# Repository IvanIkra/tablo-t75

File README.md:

<h1 align="center">Tablo T75</h1>

<p align="center">
  <b>A 7.5″ e-ink panel that shows your day at a glance — with eight real buttons for your home.</b>
</p>

<p align="center">

</p>

<p align="center">
  <a href="#whats-on-the-screen">Screen</a> ·
  <a href="#features">Features</a> ·
  <a href="#how-it-works">How it works</a> ·
  <a href="#hardware">Hardware</a> ·
  <a href="#quick-start">Quick start</a> ·
  <a href="#documentation">Docs</a>
</p>

---

Tablo is a desk or wall panel built around a 7.5″ black-and-white e-ink screen
(800×480). It shows the time, the weather for the next hours, upcoming deadlines,
news, fresh grades, the class schedule and the state of the home. Eight mechanical
keys under the screen control Home Assistant, and the tile above each key shows
whether the thing it controls is on. It runs from USB-C around the clock and reads
like a sheet of paper: no glow, no flicker.

The whole project is open: the Python service, the ESP32 firmware, the Home Assistant
integration and the 3D-printable enclosure.

## What's on the screen

<p align="center"><sub>A real frame from the service, captured in the browser emulator with demo data. Dark theme is the default.</sub></p>

| Zone | What it shows |
|---|---|
| **Clock and date** | Drawn by the board itself and updated every minute, together with the status icons (Wi-Fi, service, Home Assistant). |
| **Weather** | Now and "feels like", plus an 8-hour forecast from [Open-Meteo](https://open-meteo.com/). |
| **Deadlines** | The nearest ones first; anything due today or tomorrow is highlighted. |
| **News** | A short digest, wrapped and trimmed to fit the column. |
| **Classes** | Today's or tomorrow's classes from an iCal feed, with moved and optional ones marked. |
| **Grades** | The latest grades, with a counter of new ones. |
| **Home** | Any Home Assistant values you like: temperature, how many lights are on, the 3D printer's progress. |
| **Button tiles** | One icon per key; a filled tile means the device is on. |

<details>
<summary><b>Light theme</b></summary>
<br>

</details>

## Features

- **Smart server, dumb device.** A Python service lays out every frame with Pillow
  and streams it to the board; the ESP32 only shows it. All the logic can change
  without reflashing.
- **Partial refresh by diff.** The board compares each new frame with the one on
  the panel and redraws only what changed, with a full refresh now and then to
  clear ghosting.
- **Instant buttons.** A key press inverts its tile on the board right away, before
  the service even answers. Short and long presses can do different things.
- **Configured from Home Assistant.** Button actions, icons, Wi-Fi, data sources,
  the Home block and the screen settings are all forms in the integration.
- **Full-screen messages.** Show a message from any automation, or a sticky one that
  waits in a queue until someone presses a key.
- **Wi-Fi QR for guests.** One key shows QR codes for your networks.
- **Over-the-air updates** through the service, with a "what's new" screen after
  each new firmware version.
- **A browser emulator** of the whole board, keys included, so the screen can be
  developed without the hardware.
- **A flat printed enclosure** that hangs on the wall or stands on the desk on a
  hidden 15° leg.

<table>
  <tr>
    <td align="center" width="50%"><br><sub>A sticky message from an automation</sub></td>
    <td align="center" width="50%"><br><sub>Wi-Fi QR codes for guests</sub></td>
  </tr>
</table>

## How it works

```mermaid
flowchart LR
    subgraph sources[Data sources]
        W[Open-Meteo<br/>weather]
        I[Study data API<br/>deadlines · news · grades]
        C[iCal feed<br/>classes]
    end
    HA[Home Assistant]
    S[Tablo service<br/>Python · asyncio · Pillow]
    B[ESP32 board]
    P[(E-ink panel<br/>800×480)]

    W --> S
    I --> S
    C --> S
    HA <-->|states, config,<br/>button events| S
    S -->|1-bit frame<br/>over WebSocket| B
    B -->|key presses| S
    B --> P
```

- **The frame** is 800×480 at 1 bit per pixel: 48 000 bytes behind a small `TBLF`
  header, `1` = black. The service sends a new one only when something changes.
- **The board** keeps its own clock, date and status line, so it stays useful when
  the service is down, and it inverts the whole picture for the dark theme.
- **Buttons 1–7** do whatever Home Assistant tells them to (toggle a light, run a
  script, show the Wi-Fi QR). **Button 8** is fixed: a full refresh, or the
  diagnostics screen on a long press.
- **Secrets** live only in `.env` and in Home Assistant, never in the repository.

## Hardware

<table>
  <tr>
    <td align="center" width="33%"><br><sub>The real thing, running</sub></td>
    <td align="center" width="33%"><br><sub>On the wall</sub></td>
    <td align="center" width="33%"><br><sub>What's inside</sub></td>
  </tr>
  <tr>
    <td align="center" colspan="3"><br><sub>On the desk, on its hidden leg</sub></td>
  </tr>
</table>

| Part | What |
|---|---|
| Screen | Good Display **GDEY075T7**, 7.5″, 800×480, black and white |
| Board | Good Display **ESP32-L(C02)** with the **DESPI-C02** adapter |
| Keys | 8 × **Kailh Choc v1** Brown, low-profile |
| Power | USB-C, 5 V, any 1 A supply |
| Enclosure | 185 × 146 × 17 mm, printed in PLA or PETG without supports |

The enclosure is a parametric [OpenSCAD model](cad/tablo.scad). Ready STLs, the
list of fasteners and the print and assembly guide are in [`cad/`](cad/README.md);
the full bill of materials is in [`docs/hardware.md`](docs/hardware.md#bill-of-materials).

## Quick start

### Try it in the browser

No hardware needed: the service ships with a board emulator and a fake home.

```bash
cd service
uv sync
uv run python -m tablo --config config.yaml
```

Open <http://localhost:8765/emu>. Keys 1–8 on the keyboard press the buttons;
hold one for a long press. Checkboxes under the screen switch each block between
demo and real data. More in [`service/README.md`](service/README.md).

### Run it for real

1. **Service.** Copy `service/.env.example` to `service/.env`, fill in the tokens
   and run it with Docker: `docker compose up -d --build` in `service/`.
2. **Firmware.** Copy `firmware/include/secrets.example.h` to `secrets.h`, set
   Wi-Fi, the service address and the device token, then flash over USB:
   `pio run -e esp32 -t upload`. Later updates go over the air through the service.
3. **Home Assistant.** Copy `ha-integration/custom_components/tablo` into your HA
   config, restart HA and add the **Tablo T75** integration. See
   [`ha-integration/README.md`](ha-integration/README.md).

## Repository layout

| Path | What |
|---|---|
| [`service/`](service/) | The Python service (asyncio, aiohttp, Pillow, SQLite): data sources, layout, the device protocol, the browser emulator and the tests. |
| [`firmware/`](firmware/) | ESP32 firmware (PlatformIO + Arduino): frame buffers and diffing, the on-board clock and status line, keys, diagnostics and OTA. |
| [`ha-integration/`](ha-integration/) | The Home Assistant custom component: config forms, device triggers, `tablo.*` actions, sensors and events. |
| [`cad/`](cad/) | The enclosure in OpenSCAD, with STLs and preview renders. |
| [`docs/`](docs/) | The design documents: hardware, and the software contract split by area. |
| [`presentation/`](presentation/) | Product renders and the project presentation. |

## Documentation

| Document | About |
|---|---|
| [Product and hardware](docs/hardware.md) | What Tablo does, the screen grid, the keys, the parts and the enclosure. |
| [Architecture](docs/software/01-architecture.md) | The system and who draws which zone of the screen. |
| [Protocol](docs/software/02-protocol.md) | Board ↔ service messages, buttons and full-screen overlays. |
| [Service](docs/software/03-service.md) | Stack, layout, HTTP API and config. |
| [Data sources](docs/software/04-sources.md) | Deadlines, news, grades, classes, weather and the home. |
| [Home Assistant](docs/software/05-ha-integration.md) | The integration: forms, actions, triggers, entities. |
| [Emulator and firmware](docs/software/06-emulator-firmware.md) | The browser emulator and the ESP32 firmware. |
| [Failures and deployment](docs/software/07-failures-deploy.md) | What happens when things break, deployment and secrets. |
| [Plan](docs/software/08-plan.md) | The work plan and open questions. |

## Status

The hardware is built and running: the panel lives in its printed enclosure and
shows live frames, the clock, the status line and all eight keys, with diagnostics,
OTA updates and the post-update greeting. The firmware is at **fw-0.7**; what's
left is tuning when the panel switches from partial to full refresh.

## License

[MIT](LICENSE). Bundled third-party assets keep their own licenses:
the [Inter](service/assets/fonts/Inter-LICENSE.txt) font (SIL OFL 1.1) and the
[Material Design Icons](service/assets/mdi/LICENSE) font (Pictogrammers Free License).

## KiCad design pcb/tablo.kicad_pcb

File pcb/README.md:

# Tablo main board

KiCad 10 project for Tablo's own board: ESP32-S3 module, LiPo charger and fuel gauge, 3.3 V buck-boost, the e-paper booster circuit and the 8 key switches on one long board. The design notes, parts and pin map are in [`../docs/hardware.md`](../docs/hardware.md#custom-board-in-design); the matching enclosure is `board = "custom"` in [`../cad/`](../cad/README.md#for-the-custom-board).

Status: the schematic passes ERC; the layout is fully routed and passes DRC with the schematic parity check (left: silkscreen warnings and four thermal reliefs with one spoke). Not ordered, nothing is tried on hardware yet; see "Before ordering" below.

DRC also shows silkscreen warnings (labels over pads and the board edge) and four thermal reliefs with one spoke; none of them affects the copper.

| File | What |
|---|---|
| `tablo.kicad_sch` | The schematic (one A3 sheet, nets joined by labels) |
| `tablo.kicad_pcb` | The board: 173.5 × 41.6 mm, 4 layers (signals on F.Cu and B.Cu, solid planes: GND on In1, 3.3 V on In2) |
| `tablo.kicad_sym` | Parts missing from the KiCad libraries: TPS63802, MAX17048 |
| `tablo.pretty/` | Footprints missing from the KiCad libraries: `Kailh_Choc_V1`, `Texas_DLA0010A_VSON-HR-10_2x3mm` (from the TPS63802 datasheet's example layout) |
| `bom-parts.csv` | Manufacturer part numbers by value and footprint, and which parts are not fitted (DNP) |
| `order-notes.md` | Notes for the board house and the assembler; goes into the order package as its README |
| `tools/` | The scripts that produced the drafts, the Freerouting round trip, and the order package |

## How the drafts were made

The scripts only bootstrap the design. Once a file is edited by hand in KiCad, edit it there and do not re-run the script that wrote it, or the edits are lost.

```bash
# schematic and the custom symbols
python3 pcb/tools/gen_schematic.py
# netlist -> board: outline from the enclosure, placement, planes
kicad-cli sch export netlist --format kicadsexpr -o tablo.net pcb/tablo.kicad_sch
KPY=/Applications/KiCad/KiCad.app/Contents/Frameworks/Python.framework/Versions/Current/bin/python3
$KPY pcb/tools/gen_board.py build tablo.net
# routing: a small grid router (A* on a 0.05 mm grid; F.Cu, B.Cu and In2 when needed; vias to the planes)
$KPY pcb/tools/gen_board.py export geom.json
uv run --no-project --with numpy --with scipy python pcb/tools/route.py geom.json routes.json short
$KPY pcb/tools/gen_board.py apply routes.json
```

The router routes the signals of the fine-pitch parts first, then the power nets, then the rest; what fails gets a second pass with cheaper vias and a rip-up of the nets in its way (undone if they cannot be routed again), and GND and 3.3 V pads get short stubs to vias into the planes. `route.py finish geom.json routes.json out.json NET:REF.NUM ...` keeps a result and only tries the listed connections again. Each run takes about 10 minutes; the order (`short` or `long`) changes the result, so it is worth running both.

That draft left three connections open (around the FPC connector, where PREVGH and PREVGL boxed in VSH1 and VSL, and a piece of the 3.3 V plane cut off by tracks on In2). The committed board is that draft with part of it rerouted by [Freerouting](https://github.com/freerouting/freerouting) 2.5.0: the nets around the FPC and every net that had tracks on In2 were taken out and routed again on F.Cu and B.Cu only, so both inner layers are now solid planes. Freerouting necks power tracks down near pads and keeps only the track clearance from the FPC slot, so the script grows the slot's keepout and widens the power segments back afterwards:

```bash
$KPY pcb/tools/freeroute.py export pcb/tablo.kicad_pcb board.dsn /EPD_PREVGH /EPD_PREVGL /EPD_VSH1 /EPD_VSL \
    /VBAT /VSYS /BTN3 /BTN8 /USB_DP /USB_DN /BAT_ALRT_N /EPD_3V3 /XTAL32_P /EPD_SCK /EPD_MOSI
java -Djava.awt.headless=true -jar freerouting-2.5.0.jar -de board.dsn -do board.ses \
    --router.autorouter.max_passes=200 -mt 1 --router.copper_to_edge_clearance_um=300 \
    --gui.enabled=false --api_server.enabled=false --usage_and_diagnostic_data.disable_analytics=true
$KPY pcb/tools/freeroute.py import pcb/tablo.kicad_pcb board.ses routed.kicad_pcb
$KPY pcb/tools/freeroute.py widen routed.kicad_pcb pcb/tablo.kicad_pcb
```

Freerouting 2.5.0 needs Java 25 or newer (Homebrew's `openjdk` works); its native macOS CLI build crashes on this board. Routing the whole board from scratch with Freerouting left 16–40 connections open, so it is used only to finish.

`gen_board.py` takes the enclosure's numbers (key pitch, panel and FPC position) so that the board matches `cad/tablo.scad`: board coordinates are the enclosure's seen from the back, X = x and Y = 146 − y.

## Checks and the order package

```bash
kicad-cli sch erc --severity-all pcb/tablo.kicad_sch
kicad-cli pcb drc --schematic-parity pcb/tablo.kicad_pcb
pcb/tools/export_fab.sh      # the order package: pcb/fab/tablo-order/ and pcb/fab/tablo-order.zip
```

The order package is one archive for any board house or assembler (see `order-notes.md` for what is in it): Gerbers and drill files, a BOM with manufacturer part numbers (`bom-parts.csv`; key switches, battery pads and test pads are DNP), pick-and-place for the top side, an assembly drawing, the schematic, ODB++, a STEP model, the KiCad project, and the same for an **assembly panel**. The panel (built by `tools/order_package.py panel`) adds a 12.5 mm rail along each long edge, joined by tabs with mouse bites, with fiducials and tooling holes, for assembly lines that take boards of 70 × 70 mm or more. All files use the bottom-left corner of the board (or the panel) as 0,0. The board itself has three fiducials (FID1–FID3) for assembly without the panel.

Warnings about missing libraries only mean that KiCad's global library tables are not set up yet (KiCad does that on first start).

## Before ordering

- **Print the board 1:1 and try the real parts on it:** the Choc footprint (pin positions and the side the pins are on), the FPC connector against the panel's FPC (contact side and pin 1 — the FPC passes through the slot), the USB-C and the power switch at the enclosure's openings.
- **Measure `below_plate`** on a real switch: it sets how deep the board sits and how much room the parts have under the cover.
- **Review the power layout by eye:** both routers are generic. The loops of the TPS63802 (input cap, inductor, output cap) and of the e-paper booster (inductor, MOSFET, RESE resistor, diodes) should be short and on one layer; move parts and reroute by hand where they are not.
- **Parts in `bom-parts.csv` were checked against their datasheets** (09.11.2026): the XFL4015 terminals sit inside the 4 × 4 mm land of L1; L2 is a Sunlord SWPA4018S100MT (same land, Isat 1.3 A; the NR4018T100M is not for new designs); the crystal is the 9 pF FC-135 (Q13FC13500003). **J3 is the top-contact FH12A**: the GDEY075T7 drawing has the FPC contacts on the display side, so after the FPC bends back through the slot and over onto the parts side, its contacts face up. The FH12 and FH12A share the land pattern (Hirose catalog), so only the part changes. Stock was not checked.

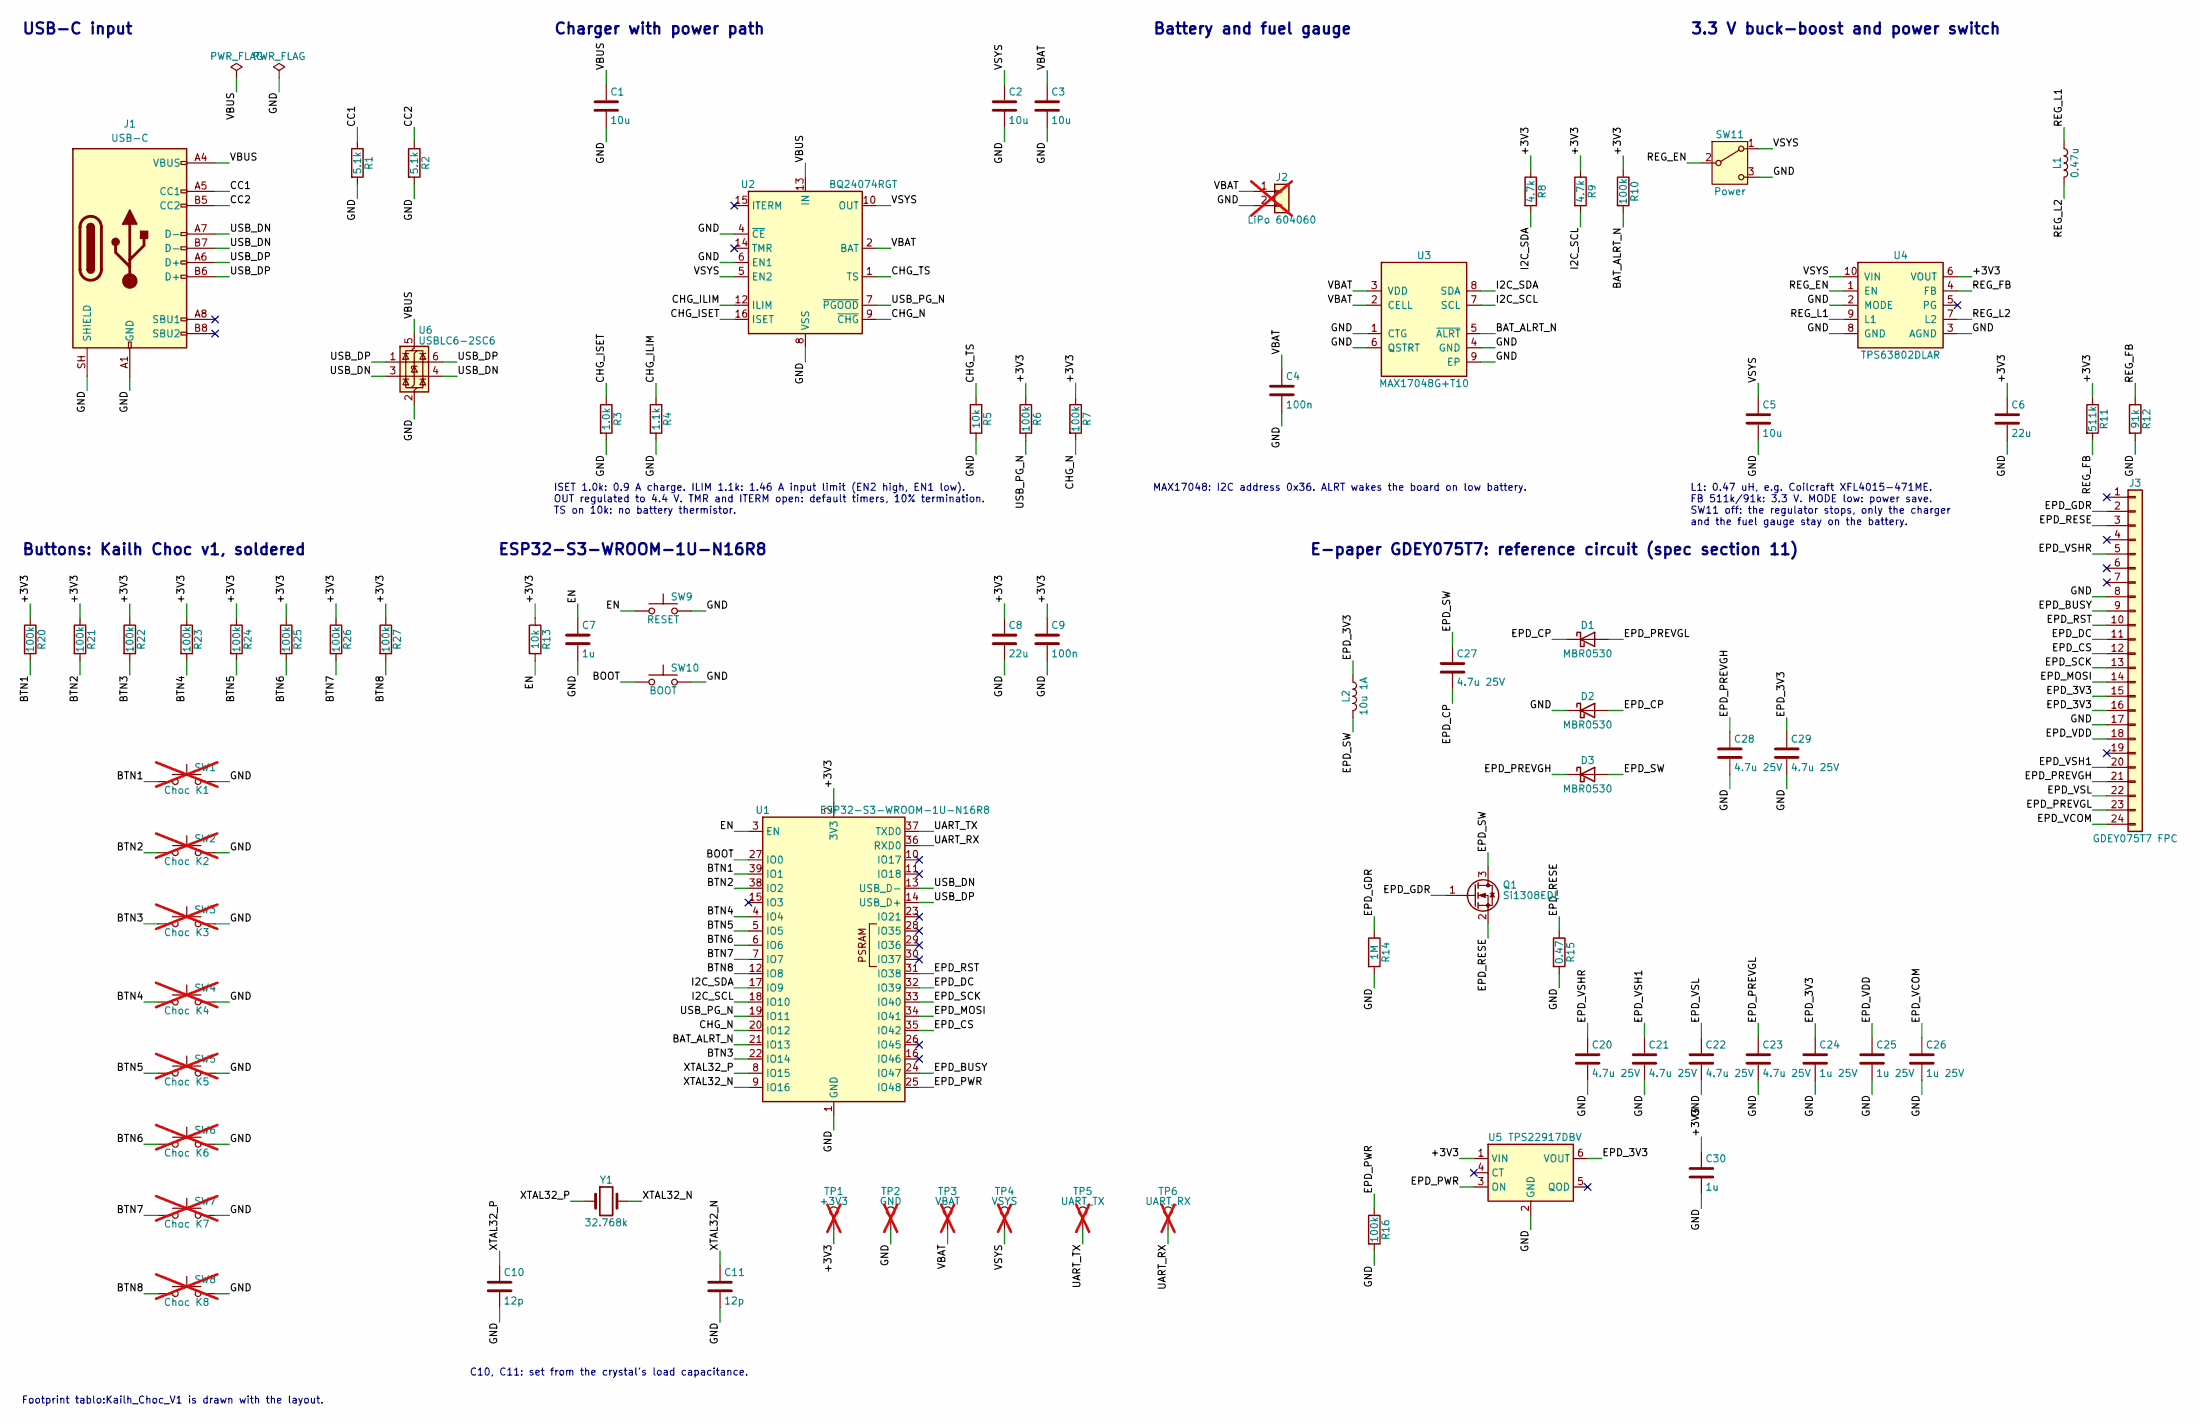
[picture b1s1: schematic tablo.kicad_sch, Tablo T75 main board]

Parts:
C1, C2, C3, C5: 10u; C_0805_2012Metric
C4, C9: 100n; C_0402_1005Metric
C6, C8: 22u; C_0805_2012Metric
C7, C30: 1u; C_0603_1608Metric
C10, C11: 12p; C_0402_1005Metric
C20, C21, C22, C23, C27, C28, C29: 4.7u 25V; C_0805_2012Metric
C24, C25, C26: 1u 25V; C_0603_1608Metric
D1, D2, D3: MBR0530; D_SOD-123
J1: USB-C; USB_C_Receptacle_HRO_TYPE-C-31-M-12
J2: LiPo 604060; SolderWire-0.25sqmm_1x02_P4.2mm_D0.65mm_OD1.7mm; not fitted
J3: GDEY075T7 FPC; Hirose_FH12-24S-0.5SH_1x24-1MP_P0.50mm_Horizontal
L1: 0.47u; L_Taiyo-Yuden_NR-40xx
L2: 10u 1A; L_Taiyo-Yuden_NR-40xx
Q1: Si1308EDL; SOT-323_SC-70
R1, R2: 5.1k; R_0402_1005Metric
R3: 1.0k; R_0402_1005Metric
R4: 1.1k; R_0402_1005Metric
R5, R13: 10k; R_0402_1005Metric
R6, R7, R10, R16, R20, R21, R22, R23, R24, R25, R26, R27: 100k; R_0402_1005Metric
R8, R9: 4.7k; R_0402_1005Metric
R11: 511k; R_0402_1005Metric
R12: 91k; R_0402_1005Metric
R14: 1M; R_0402_1005Metric
R15: 0.47; R_0603_1608Metric
SW1: Choc K1; Kailh_Choc_V1; not fitted
SW2: Choc K2; Kailh_Choc_V1; not fitted
SW3: Choc K3; Kailh_Choc_V1; not fitted
SW4: Choc K4; Kailh_Choc_V1; not fitted
SW5: Choc K5; Kailh_Choc_V1; not fitted
SW6: Choc K6; Kailh_Choc_V1; not fitted
SW7: Choc K7; Kailh_Choc_V1; not fitted
SW8: Choc K8; Kailh_Choc_V1; not fitted
SW9: RESET; SW_Push_1P1T_XKB_TS-1187A
SW10: BOOT; SW_Push_1P1T_XKB_TS-1187A
SW11: Power; SW_SPDT_PCM12
TP1: +3V3; TestPoint_Pad_D1.0mm; not fitted
TP2: GND; TestPoint_Pad_D1.0mm; not fitted
TP3: VBAT; TestPoint_Pad_D1.0mm; not fitted
TP4: VSYS; TestPoint_Pad_D1.0mm; not fitted
TP5: UART_TX; TestPoint_Pad_D1.0mm; not fitted
TP6: UART_RX; TestPoint_Pad_D1.0mm; not fitted
U1: ESP32-S3-WROOM-1U-N16R8; ESP32-S3-WROOM-1U
U2: BQ24074RGT; VQFN-16-1EP_3x3mm_P0.5mm_EP1.6x1.6mm
U3: MAX17048G+T10; TDFN-8-1EP_2x2mm_P0.5mm_EP0.8x1.2mm
U4: TPS63802DLAR; Texas_DLA0010A_VSON-HR-10_2x3mm
U5: TPS22917DBV; SOT-23-6
U6: USBLC6-2SC6; SOT-23-6
Y1: 32.768k; Crystal_SMD_3215-2Pin_3.2x1.5mm

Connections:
/+3V3: C6.1, C8.1, C9.1, C30.1, R6.1, R7.1, R8.1, R9.1, R10.1, R11.1, R13.1, R20.1, R21.1, R22.1, R23.1, R24.1, R25.1, R26.1, R27.1, TP1.1, U1.2 (3V3), U4.6 (VOUT), U5.1 (VIN)
/BAT_ALRT_N: R10.2, U1.21 (IO13), U3.5 (~ALRT)
/BOOT: SW10.1, U1.27 (IO0)
/BTN1: R20.2, SW1.1, U1.39 (IO1)
/BTN2: R21.2, SW2.1, U1.38 (IO2)
/BTN3: R22.2, SW3.1, U1.22 (IO14)
/BTN4: R23.2, SW4.1, U1.4 (IO4)
/BTN5: R24.2, SW5.1, U1.5 (IO5)
/BTN6: R25.2, SW6.1, U1.6 (IO6)
/BTN7: R26.2, SW7.1, U1.7 (IO7)
/BTN8: R27.2, SW8.1, U1.12 (IO8)
/CC1: J1.A5 (CC1), R1.1
/CC2: J1.B5 (CC2), R2.1
/CHG_ILIM: R4.1, U2.12 (ILIM)
/CHG_ISET: R3.1, U2.16 (ISET)
/CHG_N: R7.2, U1.20 (IO12), U2.9 (~CHG)
/CHG_TS: R5.1, U2.1 (TS)
/EN: C7.1, R13.2, SW9.1, U1.3 (EN)
/EPD_3V3: C24.1, C29.1, J3.15, J3.16, L2.1, U5.6 (VOUT)
/EPD_BUSY: J3.9, U1.24 (IO47)
/EPD_CP: C27.2, D1.1 (K), D2.2 (A)
/EPD_CS: J3.12, U1.35 (IO42)
/EPD_DC: J3.11, U1.32 (IO39)
/EPD_GDR: J3.2, Q1.1 (G), R14.1
/EPD_MOSI: J3.14, U1.34 (IO41)
/EPD_PREVGH: C28.1, D3.1 (K), J3.21
/EPD_PREVGL: C23.1, D1.2 (A), J3.23
/EPD_PWR: R16.1, U1.25 (IO48), U5.3 (ON)
/EPD_RESE: J3.3, Q1.2 (S), R15.1
/EPD_RST: J3.10, U1.31 (IO38)
/EPD_SCK: J3.13, U1.33 (IO40)
/EPD_SW: C27.1, D3.2 (A), L2.2, Q1.3 (D)
/EPD_VCOM: C26.1, J3.24
/EPD_VDD: C25.1, J3.18
/EPD_VSH1: C21.1, J3.20
/EPD_VSHR: C20.1, J3.5
/EPD_VSL: C22.1, J3.22
/GND: C1.2, C2.2, C3.2, C4.2, C5.2, C6.2, C7.2, C8.2, C9.2, C10.2, C11.2, C20.2, C21.2, C22.2, C23.2, C24.2, C25.2, C26.2, C28.2, C29.2, C30.2, D2.1 (K), J1.A1 (GND), J1.A12 (GND), J1.B1 (GND), J1.B12 (GND), J1.SH (SHIELD), J2.2, J3.8, J3.17, R1.2, R2.2, R3.2, R4.2, R5.2, R12.2, R14.2, R15.2, R16.2, SW1.2, SW2.2, SW3.2, SW4.2, SW5.2, SW6.2, SW7.2, SW8.2, SW9.2, SW10.2, SW11.3 (C), TP2.1, U1.1 (GND), U1.40 (GND), U1.41 (GND), U2.4 (~CE), U2.6 (EN1), U2.8 (VSS), U2.17 (VSS), U3.1 (CTG), U3.4 (GND), U3.6 (QSTRT), U3.9 (EP), U4.2 (MODE), U4.3 (AGND), U4.8 (GND), U5.2 (GND), U6.2 (GND)
/I2C_SCL: R9.2, U1.18 (IO10), U3.7 (SCL)
/I2C_SDA: R8.2, U1.17 (IO9), U3.8 (SDA)
/REG_EN: SW11.2 (B), U4.1 (EN)
/REG_FB: R11.2, R12.1, U4.4 (FB)
/REG_L1: L1.1, U4.9 (L1)
/REG_L2: L1.2, U4.7 (L2)
/UART_RX: TP6.1, U1.36 (RXD0)
/UART_TX: TP5.1, U1.37 (TXD0)
/USB_DN: J1.A7 (D-), J1.B7 (D-), U1.13 (USB_D-), U6.3 (I/O2), U6.4 (I/O2)
/USB_DP: J1.A6 (D+), J1.B6 (D+), U1.14 (USB_D+), U6.1 (I/O1), U6.6 (I/O1)
/USB_PG_N: R6.2, U1.19 (IO11), U2.7 (~PGOOD)
/VBAT: C3.1, C4.1, J2.1, TP3.1, U2.2 (BAT), U2.3 (BAT), U3.2 (CELL), U3.3 (VDD)
/VBUS: C1.1, J1.A4 (VBUS), J1.A9 (VBUS), J1.B4 (VBUS), J1.B9 (VBUS), U2.13 (IN), U6.5 (VBUS)
/VSYS: C2.1, C5.1, SW11.1 (A), TP4.1, U2.5 (EN2), U2.10 (OUT), U2.11 (OUT), U4.10 (VIN)
/XTAL32_N: C11.1, U1.9 (IO16), Y1.2
/XTAL32_P: C10.1, U1.8 (IO15), Y1.1

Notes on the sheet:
USB-C input
Charger with power path
ISET 1.0k: 0.9 A charge. ILIM 1.1k: 1.46 A input limit (EN2 high, EN1 low). OUT regulated to 4.4 V. TMR and ITERM open: default timers, 10% termination. TS on 10k: no battery thermistor.
Battery and fuel gauge
MAX17048: I2C address 0x36. ALRT wakes the board on low battery.
3.3 V buck-boost and power switch
L1: 0.47 uH, e.g. Coilcraft XFL4015-471ME. FB 511k/91k: 3.3 V. MODE low: power save. SW11 off: the regulator stops, only the charger and the fuel gauge stay on the battery.
ESP32-S3-WROOM-1U-N16R8
C10, C11: set from the crystal's load capacitance.
Buttons: Kailh Choc v1, soldered
Footprint tablo:Kailh_Choc_V1 is drawn with the layout.
E-paper GDEY075T7: reference circuit (spec section 11)

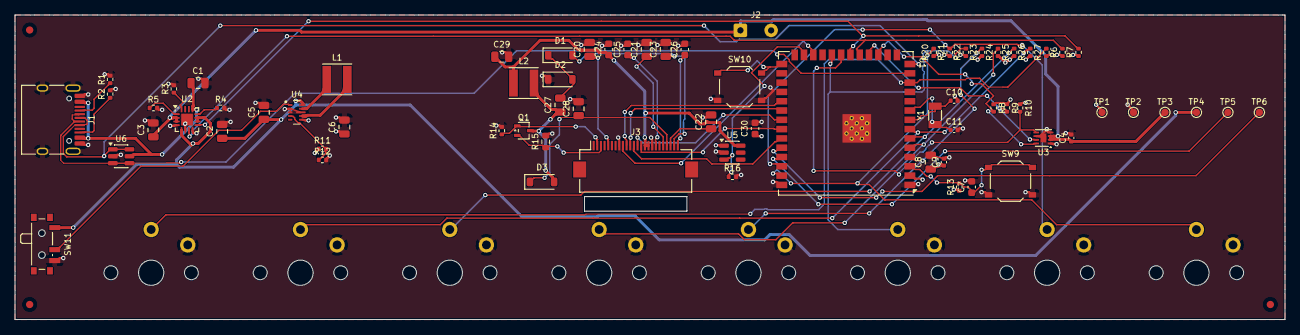
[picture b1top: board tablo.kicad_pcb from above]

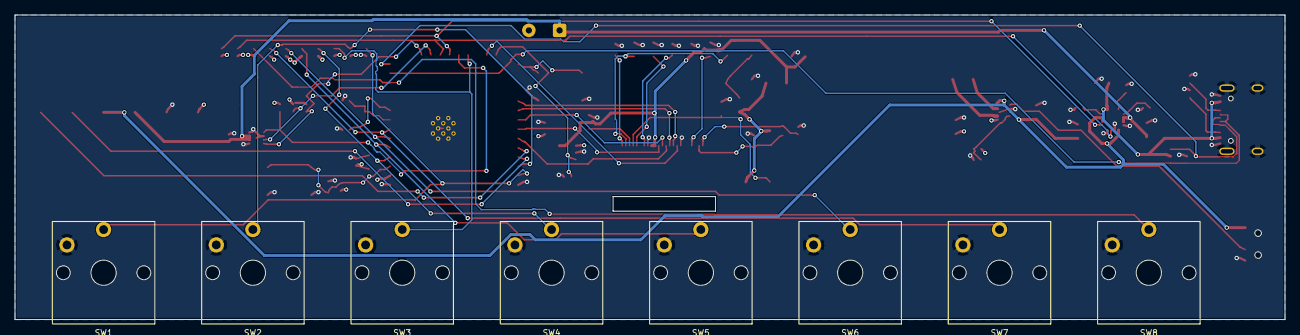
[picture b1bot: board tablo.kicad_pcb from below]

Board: 4 copper layers, 173.5 x 41.6 mm, 82 parts (8 on the bottom side), 54 nets.

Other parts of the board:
FID1, FID2, FID3: Fiducial_1mm_Mask2mm
